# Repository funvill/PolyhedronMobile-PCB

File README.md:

# PolyhedronMobile-PCB

## Rhombic Dodecahedron

- Faces: `12 Rhombus`
- Acute angle: `70.53`
- Scale: `70mm`
- Long: `scale * (3/2)`
- Short: `scale * (3 * sqrt(2) / 4)`
- EdgeLength: `scale * (3 * sqrt(6) / 8)`

- https://en.wikipedia.org/wiki/Rhombic_dodecahedron
- http://dmccooey.com/polyhedra/RhombicDodecahedron.html

## Tetragonal Trapezohedron

[Tetragonal Trapezohedron Retrospective](https://blog.abluestar.com/tetragonal-trapezohedron-retrospective/)

- Faces: `8 kites`

- https://en.wikipedia.org/wiki/Tetragonal_trapezohedron

## Dodecahedron-pcb

[Dodecahedron PCB Retrospective](https://blog.abluestar.com/dodecahedron-pcb-retrospective/)

A [Regular dodecahedron](https://en.wikipedia.org/wiki/Regular_dodecahedron) is made of 12 regular [pentagonal](https://en.wikipedia.org/wiki/Pentagon) faces.

In this project 12 pentagon PCBs with LEDS are welded together using solder at the vertexs. The hole in the center is to insert the controller and batteries into the center.

More information can be found in this post. [Dodecahedron PCB Design](https://blog.abluestar.com/dodecahedron-pcb-design)

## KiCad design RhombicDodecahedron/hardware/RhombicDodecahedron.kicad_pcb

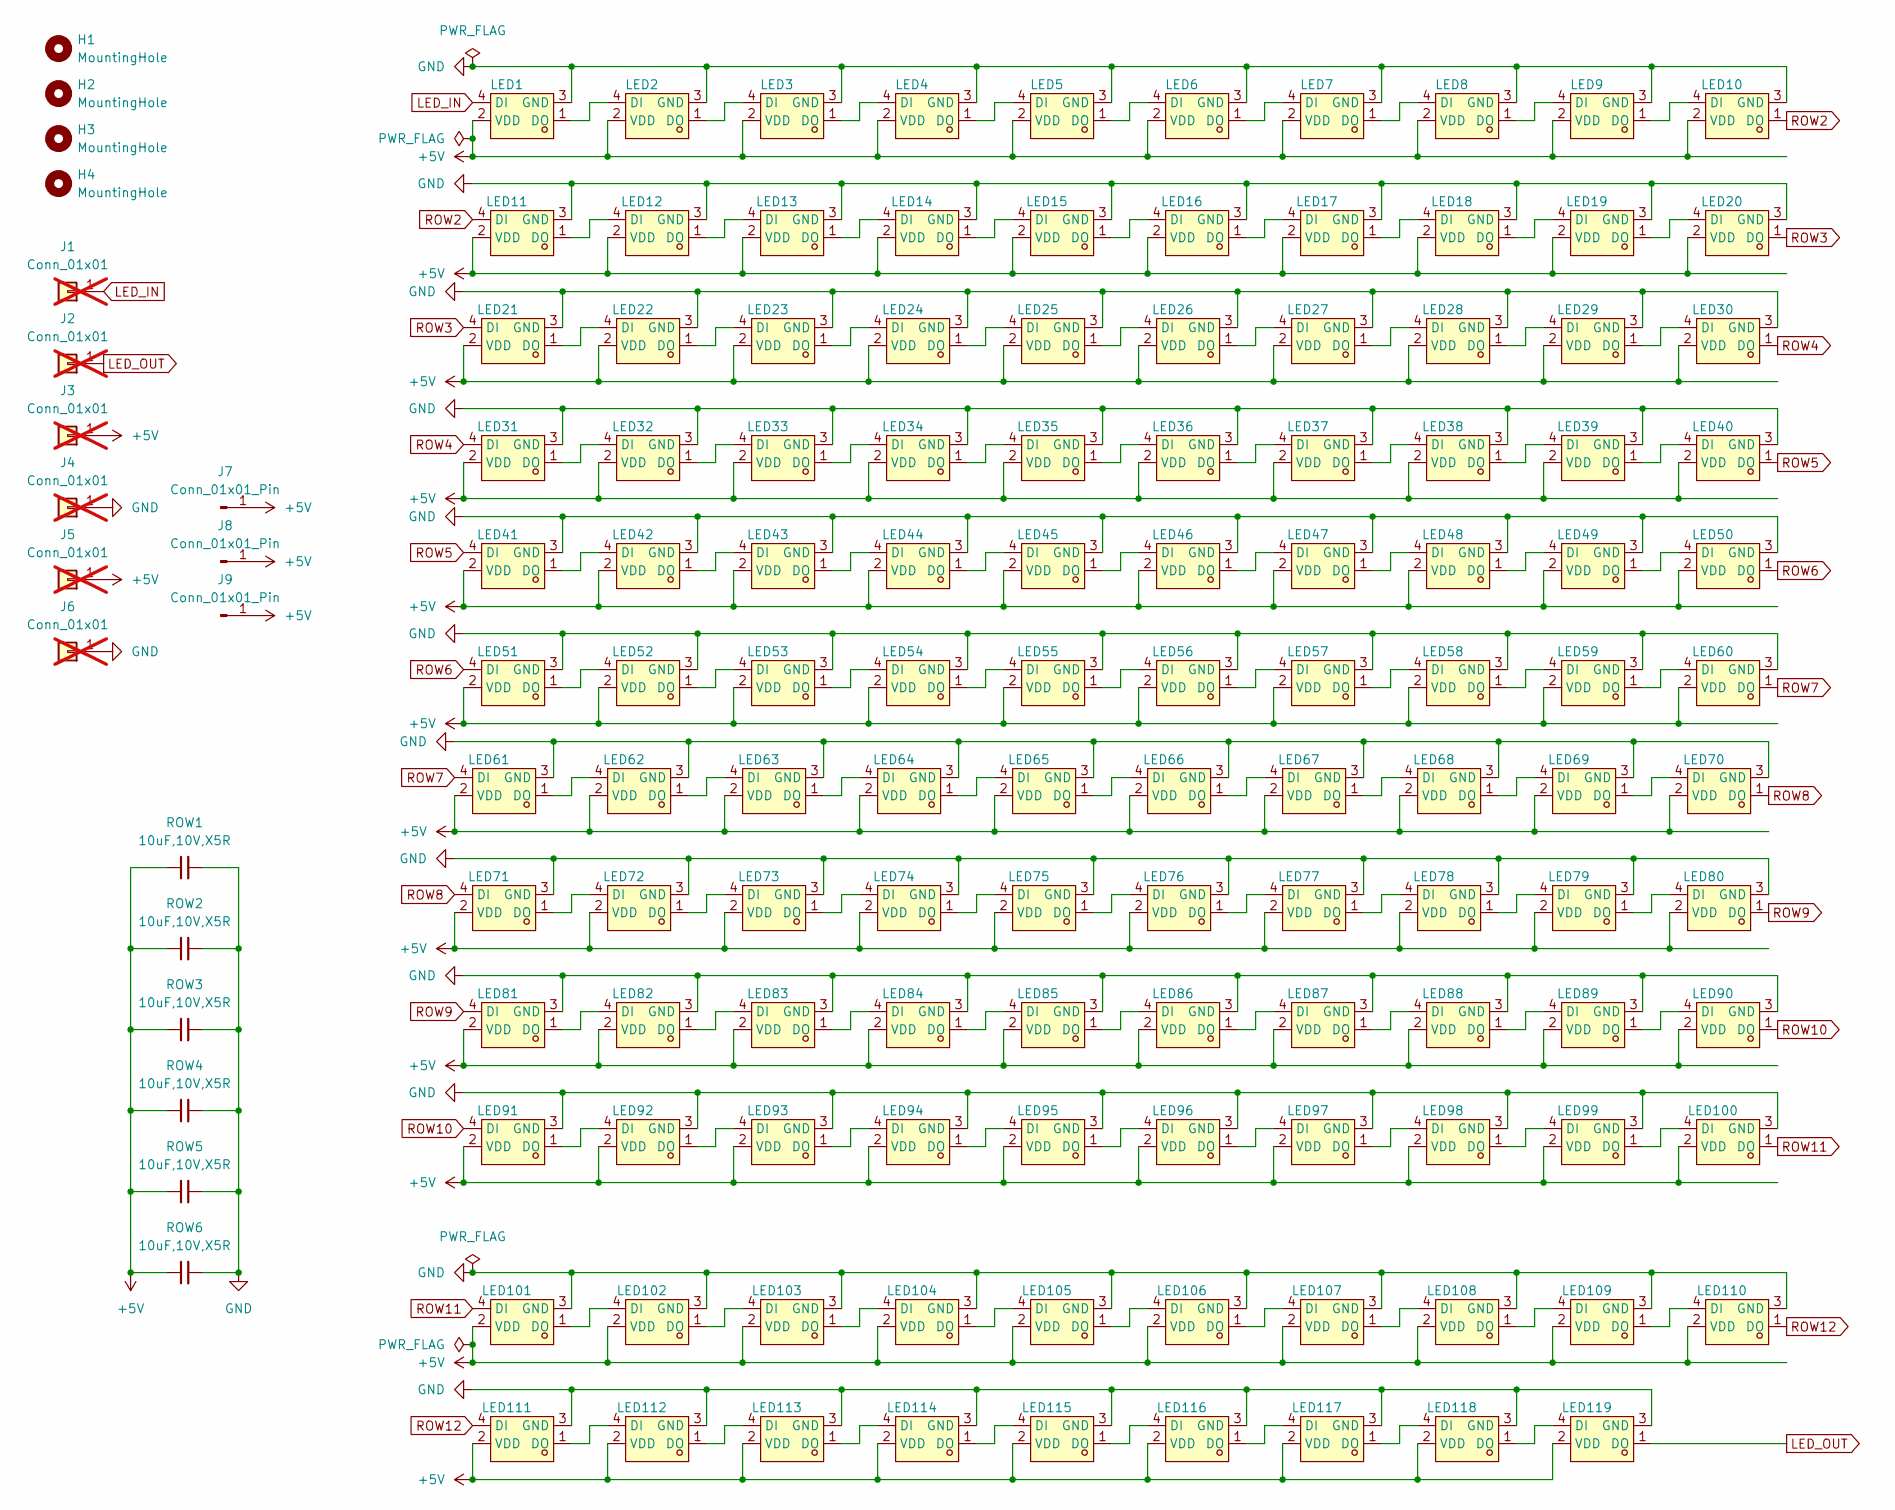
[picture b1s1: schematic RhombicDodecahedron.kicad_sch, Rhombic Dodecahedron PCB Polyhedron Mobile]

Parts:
H1, H2, H3, H4: MountingHole; MountingHole_3.2mm_M3
J1, J2, J3, J4, J5, J6: Conn_01x01; Pin_1x01_P2.54mm; not fitted
J7, J8, J9: Conn_01x01_Pin; Pin_1x01_P2.54mm_smt
LED1, LED2, LED3, LED4, LED5, LED6, LED7, LED8, LED9, LED10, LED11, LED12, LED13, LED14, LED15, LED16, LED17, LED18, LED19, LED20, LED21, LED22, LED23, LED24, LED25, LED26, LED27, LED28, LED29, LED30, LED31, LED32, LED33, LED34, LED35, LED36, LED37, LED38, LED39, LED40, LED41, LED42, LED43, LED44, LED45, LED46, LED47, LED48, LED49, LED50, LED51, LED52, LED53, LED54, LED55, LED56, LED57, LED58, LED59, LED60, LED61, LED62, LED63, LED64, LED65, LED66, LED67, LED68, LED69, LED70, LED71, LED72, LED73, LED74, LED75, LED76, LED77, LED78, LED79, LED80, LED81, LED82, LED83, LED84, LED85, LED86, LED87, LED88, LED89, LED90, LED91, LED92, LED93, LED94, LED95, LED96, LED97, LED98, LED99, LED100, LED101, LED102, LED103, LED104, LED105, LED106, LED107, LED108, LED109, LED110, LED111, LED112, LED113, LED114, LED115, LED116, LED117, LED118, LED119: XL-1615RGBC-WS2812B; LED-SMD_4P-L1.6-W1.5_XL-1615RGBC-WS2812B; LCSC Part C5349954
ROW1, ROW2, ROW3, ROW4, ROW5, ROW6: 10uF,10V,X5R; C_0402_1005Metric; MFGPN CL05A105KA5NQNC; LCSC C52923

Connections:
+5V: J3.1, J5.1, J7.1, J8.1, J9.1, LED1.2 (VDD), LED2.2 (VDD), LED3.2 (VDD), LED4.2 (VDD), LED5.2 (VDD), LED6.2 (VDD), LED7.2 (VDD), LED8.2 (VDD), LED9.2 (VDD), LED10.2 (VDD), LED11.2 (VDD), LED12.2 (VDD), LED13.2 (VDD), LED14.2 (VDD), LED15.2 (VDD), LED16.2 (VDD), LED17.2 (VDD), LED18.2 (VDD), LED19.2 (VDD), LED20.2 (VDD), LED21.2 (VDD), LED22.2 (VDD), LED23.2 (VDD), LED24.2 (VDD), LED25.2 (VDD), LED26.2 (VDD), LED27.2 (VDD), LED28.2 (VDD), LED29.2 (VDD), LED30.2 (VDD), LED31.2 (VDD), LED32.2 (VDD), LED33.2 (VDD), LED34.2 (VDD), LED35.2 (VDD), LED36.2 (VDD), LED37.2 (VDD), LED38.2 (VDD), LED39.2 (VDD), LED40.2 (VDD), LED41.2 (VDD), LED42.2 (VDD), LED43.2 (VDD), LED44.2 (VDD), LED45.2 (VDD), LED46.2 (VDD), LED47.2 (VDD), LED48.2 (VDD), LED49.2 (VDD), LED50.2 (VDD), LED51.2 (VDD), LED52.2 (VDD), LED53.2 (VDD), LED54.2 (VDD), LED55.2 (VDD), LED56.2 (VDD), LED57.2 (VDD), LED58.2 (VDD), LED59.2 (VDD), LED60.2 (VDD), LED61.2 (VDD), LED62.2 (VDD), LED63.2 (VDD), LED64.2 (VDD), LED65.2 (VDD), LED66.2 (VDD), LED67.2 (VDD), LED68.2 (VDD), LED69.2 (VDD), LED70.2 (VDD), LED71.2 (VDD), LED72.2 (VDD), LED73.2 (VDD), LED74.2 (VDD), LED75.2 (VDD), LED76.2 (VDD), LED77.2 (VDD), LED78.2 (VDD), LED79.2 (VDD), LED80.2 (VDD), LED81.2 (VDD), LED82.2 (VDD), LED83.2 (VDD), LED84.2 (VDD), LED85.2 (VDD), LED86.2 (VDD), LED87.2 (VDD), LED88.2 (VDD), LED89.2 (VDD), LED90.2 (VDD), LED91.2 (VDD), LED92.2 (VDD), LED93.2 (VDD), LED94.2 (VDD), LED95.2 (VDD), LED96.2 (VDD), LED97.2 (VDD), LED98.2 (VDD), LED99.2 (VDD), LED100.2 (VDD), LED101.2 (VDD), LED102.2 (VDD), LED103.2 (VDD), LED104.2 (VDD), LED105.2 (VDD), LED106.2 (VDD), LED107.2 (VDD), LED108.2 (VDD), LED109.2 (VDD), LED110.2 (VDD), LED111.2 (VDD), LED112.2 (VDD), LED113.2 (VDD), LED114.2 (VDD), LED115.2 (VDD), LED116.2 (VDD), LED117.2 (VDD), LED118.2 (VDD), LED119.2 (VDD), ROW1.2, ROW2.2, ROW3.2, ROW4.2, ROW5.2, ROW6.2
GND: J4.1, J6.1, LED1.3 (GND), LED2.3 (GND), LED3.3 (GND), LED4.3 (GND), LED5.3 (GND), LED6.3 (GND), LED7.3 (GND), LED8.3 (GND), LED9.3 (GND), LED10.3 (GND), LED11.3 (GND), LED12.3 (GND), LED13.3 (GND), LED14.3 (GND), LED15.3 (GND), LED16.3 (GND), LED17.3 (GND), LED18.3 (GND), LED19.3 (GND), LED20.3 (GND), LED21.3 (GND), LED22.3 (GND), LED23.3 (GND), LED24.3 (GND), LED25.3 (GND), LED26.3 (GND), LED27.3 (GND), LED28.3 (GND), LED29.3 (GND), LED30.3 (GND), LED31.3 (GND), LED32.3 (GND), LED33.3 (GND), LED34.3 (GND), LED35.3 (GND), LED36.3 (GND), LED37.3 (GND), LED38.3 (GND), LED39.3 (GND), LED40.3 (GND), LED41.3 (GND), LED42.3 (GND), LED43.3 (GND), LED44.3 (GND), LED45.3 (GND), LED46.3 (GND), LED47.3 (GND), LED48.3 (GND), LED49.3 (GND), LED50.3 (GND), LED51.3 (GND), LED52.3 (GND), LED53.3 (GND), LED54.3 (GND), LED55.3 (GND), LED56.3 (GND), LED57.3 (GND), LED58.3 (GND), LED59.3 (GND), LED60.3 (GND), LED61.3 (GND), LED62.3 (GND), LED63.3 (GND), LED64.3 (GND), LED65.3 (GND), LED66.3 (GND), LED67.3 (GND), LED68.3 (GND), LED69.3 (GND), LED70.3 (GND), LED71.3 (GND), LED72.3 (GND), LED73.3 (GND), LED74.3 (GND), LED75.3 (GND), LED76.3 (GND), LED77.3 (GND), LED78.3 (GND), LED79.3 (GND), LED80.3 (GND), LED81.3 (GND), LED82.3 (GND), LED83.3 (GND), LED84.3 (GND), LED85.3 (GND), LED86.3 (GND), LED87.3 (GND), LED88.3 (GND), LED89.3 (GND), LED90.3 (GND), LED91.3 (GND), LED92.3 (GND), LED93.3 (GND), LED94.3 (GND), LED95.3 (GND), LED96.3 (GND), LED97.3 (GND), LED98.3 (GND), LED99.3 (GND), LED100.3 (GND), LED101.3 (GND), LED102.3 (GND), LED103.3 (GND), LED104.3 (GND), LED105.3 (GND), LED106.3 (GND), LED107.3 (GND), LED108.3 (GND), LED109.3 (GND), LED110.3 (GND), LED111.3 (GND), LED112.3 (GND), LED113.3 (GND), LED114.3 (GND), LED115.3 (GND), LED116.3 (GND), LED117.3 (GND), LED118.3 (GND), LED119.3 (GND), ROW1.1, ROW2.1, ROW3.1, ROW4.1, ROW5.1, ROW6.1
LED_IN: J1.1, LED1.4 (DI)
LED_OUT: J2.1, LED119.1 (DO)
unnamed: LED1.1 (DO), LED2.4 (DI)
unnamed: LED2.1 (DO), LED3.4 (DI)
unnamed: LED3.1 (DO), LED4.4 (DI)
unnamed: LED4.1 (DO), LED5.4 (DI)
unnamed: LED5.1 (DO), LED6.4 (DI)
unnamed: LED6.1 (DO), LED7.4 (DI)
unnamed: LED7.1 (DO), LED8.4 (DI)
unnamed: LED8.1 (DO), LED9.4 (DI)
unnamed: LED9.1 (DO), LED10.4 (DI)
unnamed: LED11.1 (DO), LED12.4 (DI)
unnamed: LED12.1 (DO), LED13.4 (DI)
unnamed: LED13.1 (DO), LED14.4 (DI)
unnamed: LED14.1 (DO), LED15.4 (DI)
unnamed: LED15.1 (DO), LED16.4 (DI)
unnamed: LED16.1 (DO), LED17.4 (DI)
unnamed: LED17.1 (DO), LED18.4 (DI)
unnamed: LED18.1 (DO), LED19.4 (DI)
unnamed: LED19.1 (DO), LED20.4 (DI)
unnamed: LED21.1 (DO), LED22.4 (DI)
unnamed: LED22.1 (DO), LED23.4 (DI)
unnamed: LED23.1 (DO), LED24.4 (DI)
unnamed: LED24.1 (DO), LED25.4 (DI)
unnamed: LED25.1 (DO), LED26.4 (DI)
unnamed: LED26.1 (DO), LED27.4 (DI)
unnamed: LED27.1 (DO), LED28.4 (DI)
unnamed: LED28.1 (DO), LED29.4 (DI)
unnamed: LED29.1 (DO), LED30.4 (DI)
unnamed: LED31.1 (DO), LED32.4 (DI)
unnamed: LED32.1 (DO), LED33.4 (DI)
unnamed: LED33.1 (DO), LED34.4 (DI)
unnamed: LED34.1 (DO), LED35.4 (DI)
unnamed: LED35.1 (DO), LED36.4 (DI)
unnamed: LED36.1 (DO), LED37.4 (DI)
unnamed: LED37.1 (DO), LED38.4 (DI)
unnamed: LED38.1 (DO), LED39.4 (DI)
unnamed: LED39.1 (DO), LED40.4 (DI)
unnamed: LED41.1 (DO), LED42.4 (DI)
unnamed: LED42.1 (DO), LED43.4 (DI)
unnamed: LED43.1 (DO), LED44.4 (DI)
unnamed: LED44.1 (DO), LED45.4 (DI)
unnamed: LED45.1 (DO), LED46.4 (DI)
unnamed: LED46.1 (DO), LED47.4 (DI)
unnamed: LED47.1 (DO), LED48.4 (DI)
unnamed: LED48.1 (DO), LED49.4 (DI)
unnamed: LED49.1 (DO), LED50.4 (DI)
unnamed: LED51.1 (DO), LED52.4 (DI)
unnamed: LED52.1 (DO), LED53.4 (DI)
unnamed: LED53.1 (DO), LED54.4 (DI)
unnamed: LED54.1 (DO), LED55.4 (DI)
unnamed: LED55.1 (DO), LED56.4 (DI)
unnamed: LED56.1 (DO), LED57.4 (DI)
unnamed: LED57.1 (DO), LED58.4 (DI)
unnamed: LED58.1 (DO), LED59.4 (DI)
unnamed: LED59.1 (DO), LED60.4 (DI)
unnamed: LED61.1 (DO), LED62.4 (DI)
unnamed: LED62.1 (DO), LED63.4 (DI)
unnamed: LED63.1 (DO), LED64.4 (DI)
unnamed: LED64.1 (DO), LED65.4 (DI)
unnamed: LED65.1 (DO), LED66.4 (DI)
unnamed: LED66.1 (DO), LED67.4 (DI)
unnamed: LED67.1 (DO), LED68.4 (DI)
unnamed: LED68.1 (DO), LED69.4 (DI)
unnamed: LED69.1 (DO), LED70.4 (DI)
unnamed: LED71.1 (DO), LED72.4 (DI)
unnamed: LED72.1 (DO), LED73.4 (DI)
unnamed: LED73.1 (DO), LED74.4 (DI)
unnamed: LED74.1 (DO), LED75.4 (DI)
unnamed: LED75.1 (DO), LED76.4 (DI)
unnamed: LED76.1 (DO), LED77.4 (DI)
unnamed: LED77.1 (DO), LED78.4 (DI)
unnamed: LED78.1 (DO), LED79.4 (DI)
unnamed: LED79.1 (DO), LED80.4 (DI)
unnamed: LED81.1 (DO), LED82.4 (DI)
unnamed: LED82.1 (DO), LED83.4 (DI)
unnamed: LED83.1 (DO), LED84.4 (DI)
unnamed: LED84.1 (DO), LED85.4 (DI)
unnamed: LED85.1 (DO), LED86.4 (DI)
unnamed: LED86.1 (DO), LED87.4 (DI)
unnamed: LED87.1 (DO), LED88.4 (DI)
unnamed: LED88.1 (DO), LED89.4 (DI)
unnamed: LED89.1 (DO), LED90.4 (DI)
unnamed: LED91.1 (DO), LED92.4 (DI)
unnamed: LED92.1 (DO), LED93.4 (DI)
unnamed: LED93.1 (DO), LED94.4 (DI)
unnamed: LED94.1 (DO), LED95.4 (DI)
unnamed: LED95.1 (DO), LED96.4 (DI)
unnamed: LED96.1 (DO), LED97.4 (DI)
unnamed: LED97.1 (DO), LED98.4 (DI)
unnamed: LED98.1 (DO), LED99.4 (DI)
unnamed: LED99.1 (DO), LED100.4 (DI)
unnamed: LED101.1 (DO), LED102.4 (DI)
unnamed: LED102.1 (DO), LED103.4 (DI)
unnamed: LED103.1 (DO), LED104.4 (DI)
unnamed: LED104.1 (DO), LED105.4 (DI)
unnamed: LED105.1 (DO), LED106.4 (DI)
unnamed: LED106.1 (DO), LED107.4 (DI)
unnamed: LED107.1 (DO), LED108.4 (DI)
unnamed: LED108.1 (DO), LED109.4 (DI)
unnamed: LED109.1 (DO), LED110.4 (DI)
unnamed: LED111.1 (DO), LED112.4 (DI)
unnamed: LED112.1 (DO), LED113.4 (DI)
unnamed: LED113.1 (DO), LED114.4 (DI)
unnamed: LED114.1 (DO), LED115.4 (DI)
unnamed: LED115.1 (DO), LED116.4 (DI)
unnamed: LED116.1 (DO), LED117.4 (DI)
unnamed: LED117.1 (DO), LED118.4 (DI)
unnamed: LED118.1 (DO), LED119.4 (DI)
ROW2: LED10.1 (DO), LED11.4 (DI)
ROW3: LED20.1 (DO), LED21.4 (DI)
ROW4: LED30.1 (DO), LED31.4 (DI)
ROW5: LED40.1 (DO), LED41.4 (DI)
ROW6: LED50.1 (DO), LED51.4 (DI)
ROW7: LED60.1 (DO), LED61.4 (DI)
ROW8: LED70.1 (DO), LED71.4 (DI)
ROW9: LED80.1 (DO), LED81.4 (DI)
ROW10: LED90.1 (DO), LED91.4 (DI)
ROW11: LED100.1 (DO), LED101.4 (DI)
ROW12: LED110.1 (DO), LED111.4 (DI)

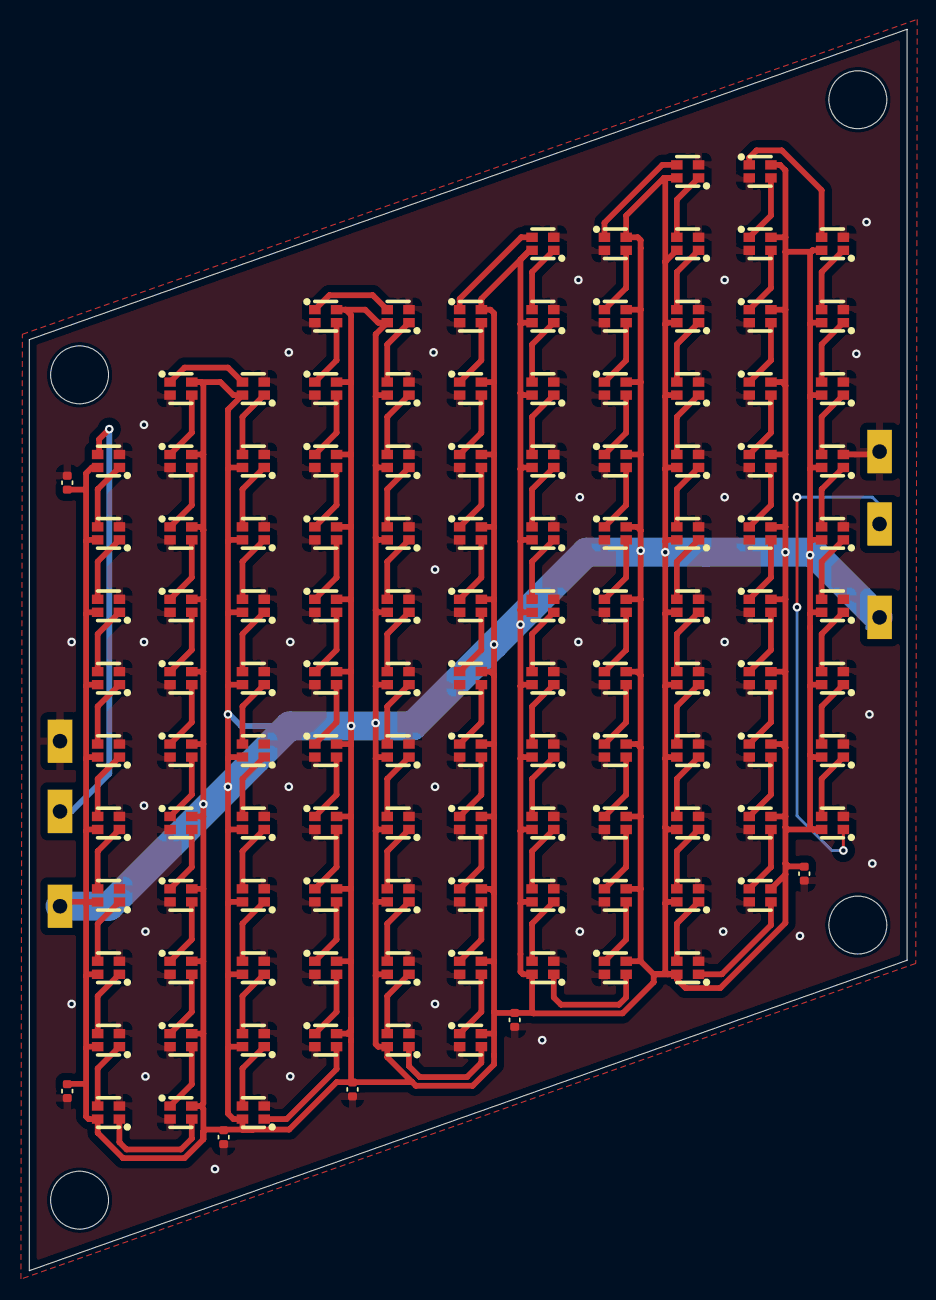
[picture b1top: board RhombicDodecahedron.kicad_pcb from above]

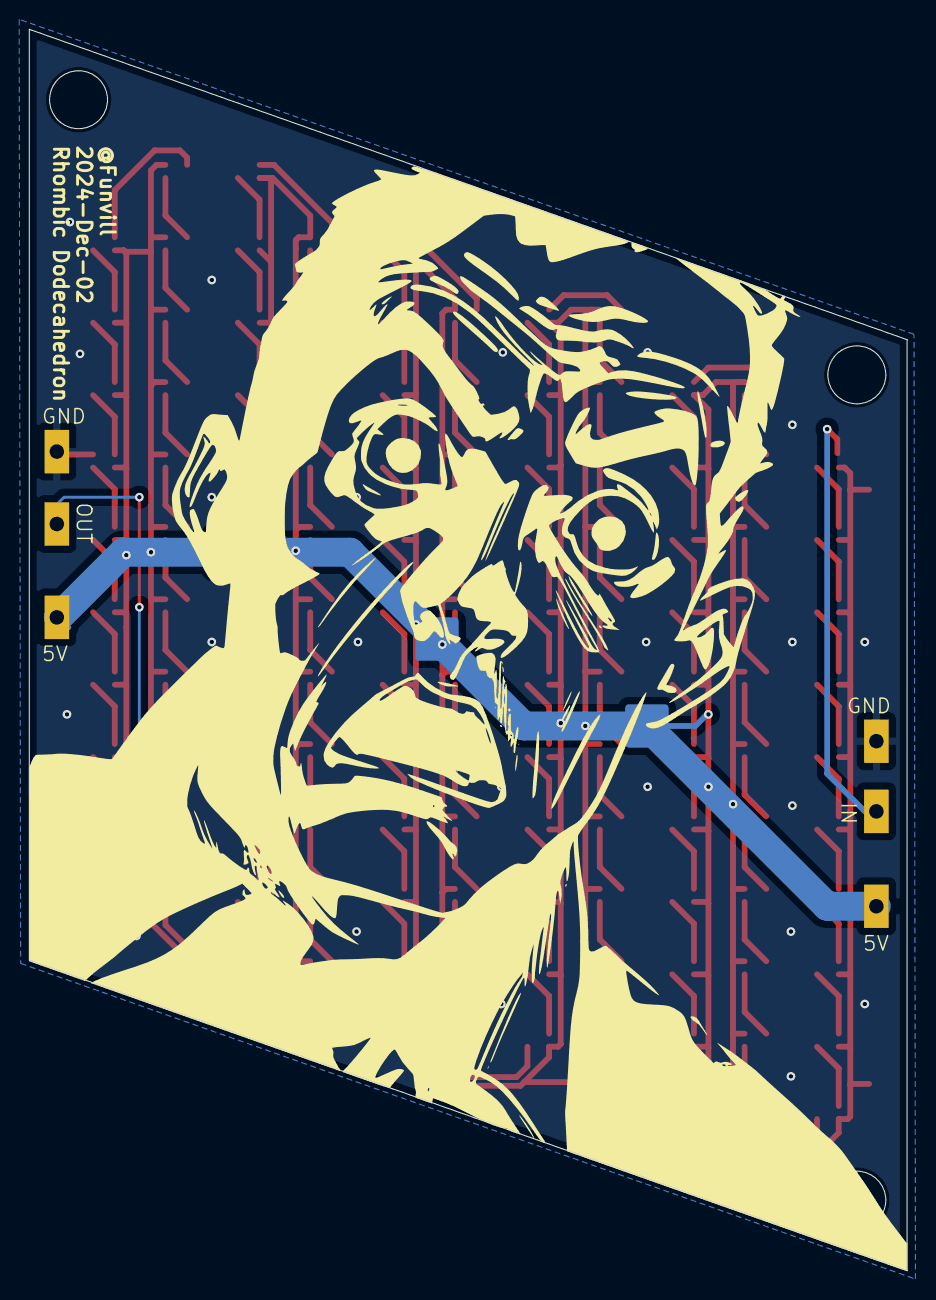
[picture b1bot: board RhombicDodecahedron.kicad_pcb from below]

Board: 2 copper layers, 60.6 x 85.7 mm, 138 parts (3 on the bottom side), 122 nets.

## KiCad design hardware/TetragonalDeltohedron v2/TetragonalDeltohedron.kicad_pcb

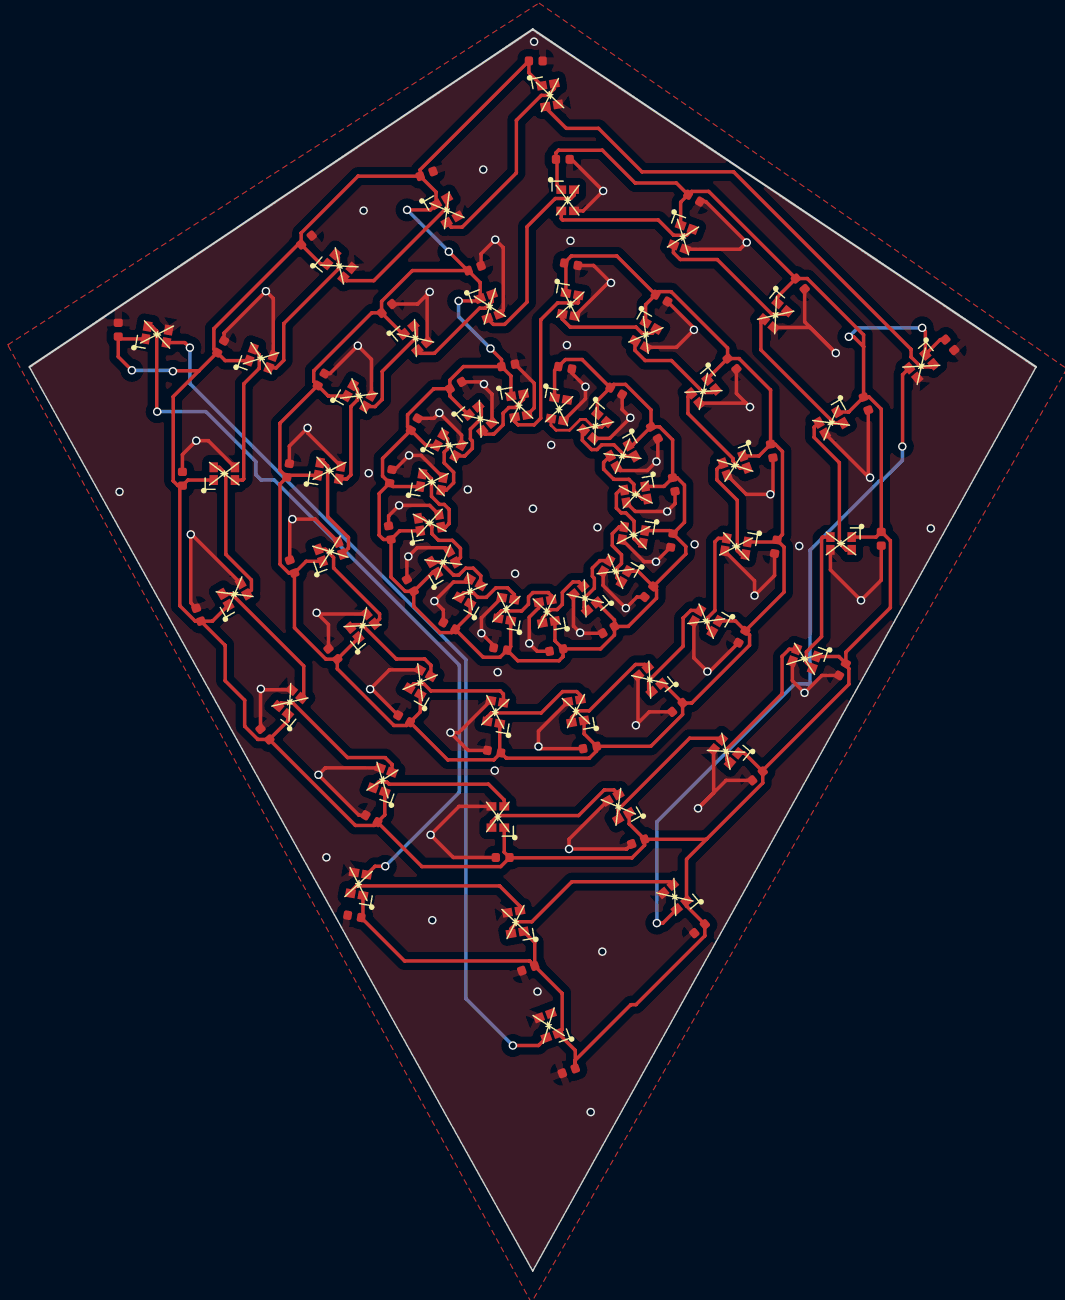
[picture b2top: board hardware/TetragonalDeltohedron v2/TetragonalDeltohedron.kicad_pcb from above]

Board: 2 copper layers, 71.1 x 87.7 mm, 110 parts (0 on the bottom side), 56 nets.

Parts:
C1, C2, C3, C4, C5, C6, C7, C8, C9, C10, C11, C12, C13, C14, C15, C16, C17, C18, C19, C20, C21, C22, C23, C24, C25, C26, C27, C28, C29, C30, C31, C32, C33, C34, C35, C36, C37, C38, C39, C40, C41, C42, C43, C44, C45, C46, C47, C48, C49, C50, C51, C52, C53, C54, C55: 1uF,25V,X5R; C_0402_1005Metric
U1, U2, U3, U4, U5, U6, U7, U8, U9, U10, U11, U12, U13, U14, U15, U16, U17, U18, U19, U20, U21, U22, U23, U24, U25, U26, U27, U28, U29, U30, U31, U32, U33, U34, U35, U36, U37, U38, U39, U40, U41, U42, U43, U44, U45, U46, U47, U48, U49, U50, U51, U52, U53, U54, U55: XL-0807RGBC-WS2812B

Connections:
+5V: C1.1, C2.1, C3.1, C4.1, C5.1, C6.1, C7.1, C8.1, C9.1, C10.1, C11.1, C12.1, C13.1, C14.1, C15.1, C16.1, C17.1, C18.1, C19.1, C20.1, C21.1, C22.1, C23.1, C24.1, C25.1, C26.1, C27.1, C28.1, C29.1, C30.1, C31.1, C32.1, C33.1, C34.1, C35.1, C36.1, C37.1, C38.1, C39.1, C40.1, C41.1, C42.1, C43.1, C44.1, C45.1, C46.1, C47.1, C48.1, C49.1, C50.1, C51.1, C52.1, C53.1, C54.1, C55.1, U1.1 (VDD), U2.1 (VDD), U3.1 (VDD), U4.1 (VDD), U5.1 (VDD), U6.1 (VDD), U7.1 (VDD), U8.1 (VDD), U9.1 (VDD), U10.1 (VDD), U11.1 (VDD), U12.1 (VDD), U13.1 (VDD), U14.1 (VDD), U15.1 (VDD), U16.1 (VDD), U17.1 (VDD), U18.1 (VDD), U19.1 (VDD), U20.1 (VDD), U21.1 (VDD), U22.1 (VDD), U23.1 (VDD), U24.1 (VDD), U25.1 (VDD), U26.1 (VDD), U27.1 (VDD), U28.1 (VDD), U29.1 (VDD), U30.1 (VDD), U31.1 (VDD), U32.1 (VDD), U33.1 (VDD), U34.1 (VDD), U35.1 (VDD), U36.1 (VDD), U37.1 (VDD), U38.1 (VDD), U39.1 (VDD), U40.1 (VDD), U41.1 (VDD), U42.1 (VDD), U43.1 (VDD), U44.1 (VDD), U45.1 (VDD), U46.1 (VDD), U47.1 (VDD), U48.1 (VDD), U49.1 (VDD), U50.1 (VDD), U51.1 (VDD), U52.1 (VDD), U53.1 (VDD), U54.1 (VDD), U55.1 (VDD)
GND: C1.2, C2.2, C3.2, C4.2, C5.2, C6.2, C7.2, C8.2, C9.2, C10.2, C11.2, C12.2, C13.2, C14.2, C15.2, C16.2, C17.2, C18.2, C19.2, C20.2, C21.2, C22.2, C23.2, C24.2, C25.2, C26.2, C27.2, C28.2, C29.2, C30.2, C31.2, C32.2, C33.2, C34.2, C35.2, C36.2, C37.2, C38.2, C39.2, C40.2, C41.2, C42.2, C43.2, C44.2, C45.2, C46.2, C47.2, C48.2, C49.2, C50.2, C51.2, C52.2, C53.2, C54.2, C55.2, U1.3 (GND), U2.3 (GND), U3.3 (GND), U4.3 (GND), U5.3 (GND), U6.3 (GND), U7.3 (GND), U8.3 (GND), U9.3 (GND), U10.3 (GND), U11.3 (GND), U12.3 (GND), U13.3 (GND), U14.3 (GND), U15.3 (GND), U16.3 (GND), U17.3 (GND), U18.3 (GND), U19.3 (GND), U20.3 (GND), U21.3 (GND), U22.3 (GND), U23.3 (GND), U24.3 (GND), U25.3 (GND), U26.3 (GND), U27.3 (GND), U28.3 (GND), U29.3 (GND), U30.3 (GND), U31.3 (GND), U32.3 (GND), U33.3 (GND), U34.3 (GND), U35.3 (GND), U36.3 (GND), U37.3 (GND), U38.3 (GND), U39.3 (GND), U40.3 (GND), U41.3 (GND), U42.3 (GND), U43.3 (GND), U44.3 (GND), U45.3 (GND), U46.3 (GND), U47.3 (GND), U48.3 (GND), U49.3 (GND), U50.3 (GND), U51.3 (GND), U52.3 (GND), U53.3 (GND), U54.3 (GND), U55.3 (GND)
unnamed: U1.2 (DOUT), U2.4 (DIN)
unnamed: U2.2 (DOUT), U3.4 (DIN)
unnamed: U3.2 (DOUT), U4.4 (DIN)
unnamed: U4.2 (DOUT), U5.4 (DIN)
unnamed: U5.2 (DOUT), U6.4 (DIN)
unnamed: U6.2 (DOUT), U7.4 (DIN)
unnamed: U7.2 (DOUT), U8.4 (DIN)
unnamed: U8.2 (DOUT), U9.4 (DIN)
unnamed: U9.2 (DOUT), U10.4 (DIN)
unnamed: U10.2 (DOUT), U11.4 (DIN)
unnamed: U11.2 (DOUT), U12.4 (DIN)
unnamed: U12.2 (DOUT), U13.4 (DIN)
unnamed: U13.2 (DOUT), U14.4 (DIN)
unnamed: U14.2 (DOUT), U15.4 (DIN)
unnamed: U15.2 (DOUT), U16.4 (DIN)
unnamed: U17.2 (DOUT), U18.4 (DIN)
unnamed: U18.2 (DOUT), U19.4 (DIN)
unnamed: U19.2 (DOUT), U20.4 (DIN)
unnamed: U20.2 (DOUT), U21.4 (DIN)
unnamed: U21.2 (DOUT), U22.4 (DIN)
unnamed: U22.2 (DOUT), U23.4 (DIN)
unnamed: U23.2 (DOUT), U24.4 (DIN)
unnamed: U24.2 (DOUT), U25.4 (DIN)
unnamed: U25.2 (DOUT), U26.4 (DIN)
unnamed: U26.2 (DOUT), U27.4 (DIN)
unnamed: U27.2 (DOUT), U28.4 (DIN)
unnamed: U28.2 (DOUT), U29.4 (DIN)
unnamed: U29.2 (DOUT), U30.4 (DIN)
unnamed: U30.2 (DOUT), U31.4 (DIN)
unnamed: U31.2 (DOUT), U32.4 (DIN)
unnamed: U33.2 (DOUT), U34.4 (DIN)
unnamed: U34.2 (DOUT), U35.4 (DIN)
unnamed: U35.2 (DOUT), U36.4 (DIN)
unnamed: U36.2 (DOUT), U37.4 (DIN)
unnamed: U37.2 (DOUT), U38.4 (DIN)
unnamed: U38.2 (DOUT), U39.4 (DIN)
unnamed: U39.2 (DOUT), U40.4 (DIN)
unnamed: U40.2 (DOUT), U41.4 (DIN)
unnamed: U41.2 (DOUT), U42.4 (DIN)
unnamed: U42.2 (DOUT), U43.4 (DIN)
unnamed: U43.2 (DOUT), U44.4 (DIN)
unnamed: U44.2 (DOUT), U45.4 (DIN)
unnamed: U45.2 (DOUT), U46.4 (DIN)
unnamed: U46.2 (DOUT), U47.4 (DIN)
unnamed: U47.2 (DOUT), U48.4 (DIN)
unnamed: U49.2 (DOUT), U50.4 (DIN)
unnamed: U50.2 (DOUT), U51.4 (DIN)
unnamed: U51.2 (DOUT), U52.4 (DIN)
unnamed: U52.2 (DOUT), U53.4 (DIN)
unnamed: U53.2 (DOUT), U54.4 (DIN)
unnamed: U54.2 (DOUT), U55.4 (DIN)
ROW_02: U16.2 (DOUT), U17.4 (DIN)
ROW_03: U32.2 (DOUT), U33.4 (DIN)
ROW_04: U48.2 (DOUT), U49.4 (DIN)

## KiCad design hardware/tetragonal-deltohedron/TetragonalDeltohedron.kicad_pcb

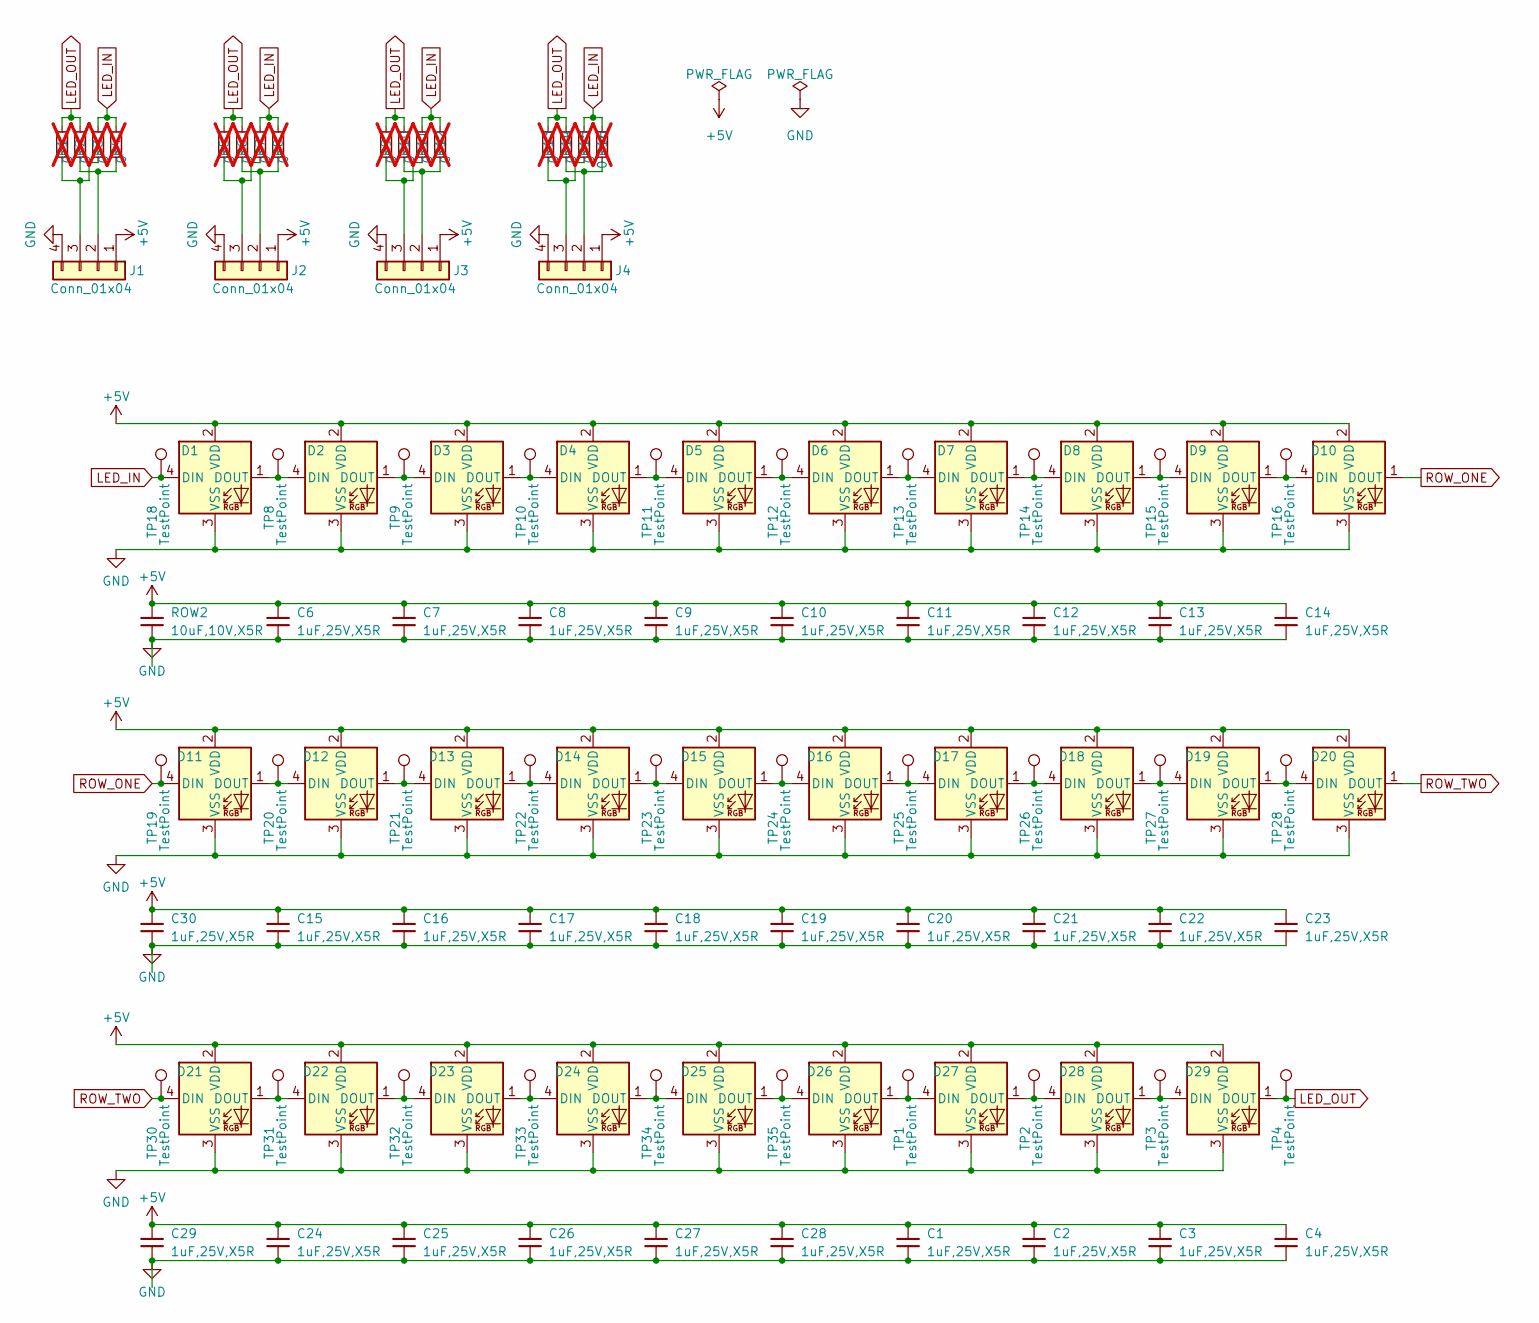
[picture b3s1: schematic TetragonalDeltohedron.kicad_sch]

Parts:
C1, C2, C3, C4, C6, C7, C8, C9, C10, C11, C12, C13, C14, C15, C16, C17, C18, C19, C20, C21, C22, C23, C24, C25, C26, C27, C28, C29, C30: 1uF,25V,X5R; C_0603_1608Metric; MFGPN CL05A105KA5NQNC; LCSC C52923
D1, D2, D3, D4, D5, D6, D7, D8, D9, D10, D11, D12, D13, D14, D15, D16, D17, D18, D19, D20, D21, D22, D23, D24, D25, D26, D27, D28, D29: XL-1010RGBC-WS2812B; LCSC C5349953
J1, J2, J3, J4: Conn_01x04; dodecahedron_corner
R1, R2, R3, R4, R5, R6, R7, R8, R9, R10, R11, R12, R13, R14, R15, R16: 0; R_0402_1005Metric; MFGPN 0402WGF0000TCE; LCSC C17168; not fitted
ROW2: 10uF,10V,X5R; C_0603_1608Metric; MFGPN CL05A105KA5NQNC; LCSC C52923
TP1, TP2, TP3, TP4, TP8, TP9, TP10, TP11, TP12, TP13, TP14, TP15, TP16, TP18, TP19, TP20, TP21, TP22, TP23, TP24, TP25, TP26, TP27, TP28, TP30, TP31, TP32, TP33, TP34, TP35: TestPoint; SWS-Testpoint-Bug-SM-2.4mm

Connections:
+5V: C1.1, C2.1, C3.1, C4.1, C6.1, C7.1, C8.1, C9.1, C10.1, C11.1, C12.1, C13.1, C14.1, C15.1, C16.1, C17.1, C18.1, C19.1, C20.1, C21.1, C22.1, C23.1, C24.1, C25.1, C26.1, C27.1, C28.1, C29.1, C30.1, D1.2 (VDD), D2.2 (VDD), D3.2 (VDD), D4.2 (VDD), D5.2 (VDD), D6.2 (VDD), D7.2 (VDD), D8.2 (VDD), D9.2 (VDD), D10.2 (VDD), D11.2 (VDD), D12.2 (VDD), D13.2 (VDD), D14.2 (VDD), D15.2 (VDD), D16.2 (VDD), D17.2 (VDD), D18.2 (VDD), D19.2 (VDD), D20.2 (VDD), D21.2 (VDD), D22.2 (VDD), D23.2 (VDD), D24.2 (VDD), D25.2 (VDD), D26.2 (VDD), D27.2 (VDD), D28.2 (VDD), D29.2 (VDD), J1.1, J2.1, J3.1, J4.1, ROW2.2
GND: C1.2, C2.2, C3.2, C4.2, C6.2, C7.2, C8.2, C9.2, C10.2, C11.2, C12.2, C13.2, C14.2, C15.2, C16.2, C17.2, C18.2, C19.2, C20.2, C21.2, C22.2, C23.2, C24.2, C25.2, C26.2, C27.2, C28.2, C29.2, C30.2, D1.3 (VSS), D2.3 (VSS), D3.3 (VSS), D4.3 (VSS), D5.3 (VSS), D6.3 (VSS), D7.3 (VSS), D8.3 (VSS), D9.3 (VSS), D10.3 (VSS), D11.3 (VSS), D12.3 (VSS), D13.3 (VSS), D14.3 (VSS), D15.3 (VSS), D16.3 (VSS), D17.3 (VSS), D18.3 (VSS), D19.3 (VSS), D20.3 (VSS), D21.3 (VSS), D22.3 (VSS), D23.3 (VSS), D24.3 (VSS), D25.3 (VSS), D26.3 (VSS), D27.3 (VSS), D28.3 (VSS), D29.3 (VSS), J1.4, J2.4, J3.4, J4.4, ROW2.1
LED_IN: D1.4 (DIN), R3.1, R4.1, R7.1, R8.1, R11.1, R12.1, R15.1, R16.1, TP18.1
LED_OUT: D29.1 (DOUT), R1.1, R2.1, R5.1, R6.1, R9.1, R10.1, R13.1, R14.1, TP4.1
unnamed: D1.1 (DOUT), D2.4 (DIN), TP8.1
unnamed: D2.1 (DOUT), D3.4 (DIN), TP9.1
unnamed: D3.1 (DOUT), D4.4 (DIN), TP10.1
unnamed: D4.1 (DOUT), D5.4 (DIN), TP11.1
unnamed: D5.1 (DOUT), D6.4 (DIN), TP12.1
unnamed: D6.1 (DOUT), D7.4 (DIN), TP13.1
unnamed: D7.1 (DOUT), D8.4 (DIN), TP14.1
unnamed: D8.1 (DOUT), D9.4 (DIN), TP15.1
unnamed: D9.1 (DOUT), D10.4 (DIN), TP16.1
unnamed: D11.1 (DOUT), D12.4 (DIN), TP20.1
unnamed: D12.1 (DOUT), D13.4 (DIN), TP21.1
unnamed: D13.1 (DOUT), D14.4 (DIN), TP22.1
unnamed: D14.1 (DOUT), D15.4 (DIN), TP23.1
unnamed: D15.1 (DOUT), D16.4 (DIN), TP24.1
unnamed: D16.1 (DOUT), D17.4 (DIN), TP25.1
unnamed: D17.1 (DOUT), D18.4 (DIN), TP26.1
unnamed: D18.1 (DOUT), D19.4 (DIN), TP27.1
unnamed: D19.1 (DOUT), D20.4 (DIN), TP28.1
unnamed: D21.1 (DOUT), D22.4 (DIN), TP31.1
unnamed: D22.1 (DOUT), D23.4 (DIN), TP32.1
unnamed: D23.1 (DOUT), D24.4 (DIN), TP33.1
unnamed: D24.1 (DOUT), D25.4 (DIN), TP34.1
unnamed: D25.1 (DOUT), D26.4 (DIN), TP35.1
unnamed: D26.1 (DOUT), D27.4 (DIN), TP1.1
unnamed: D27.1 (DOUT), D28.4 (DIN), TP2.1
unnamed: D28.1 (DOUT), D29.4 (DIN), TP3.1
unnamed: J1.2, R2.2, R4.2
unnamed: J1.3, R1.2, R3.2
unnamed: J2.2, R6.2, R8.2
unnamed: J2.3, R5.2, R7.2
unnamed: J3.2, R10.2, R12.2
unnamed: J3.3, R9.2, R11.2
unnamed: J4.2, R14.2, R16.2
unnamed: J4.3, R13.2, R15.2
ROW_ONE: D10.1 (DOUT), D11.4 (DIN), TP19.1
ROW_TWO: D20.1 (DOUT), D21.4 (DIN), TP30.1

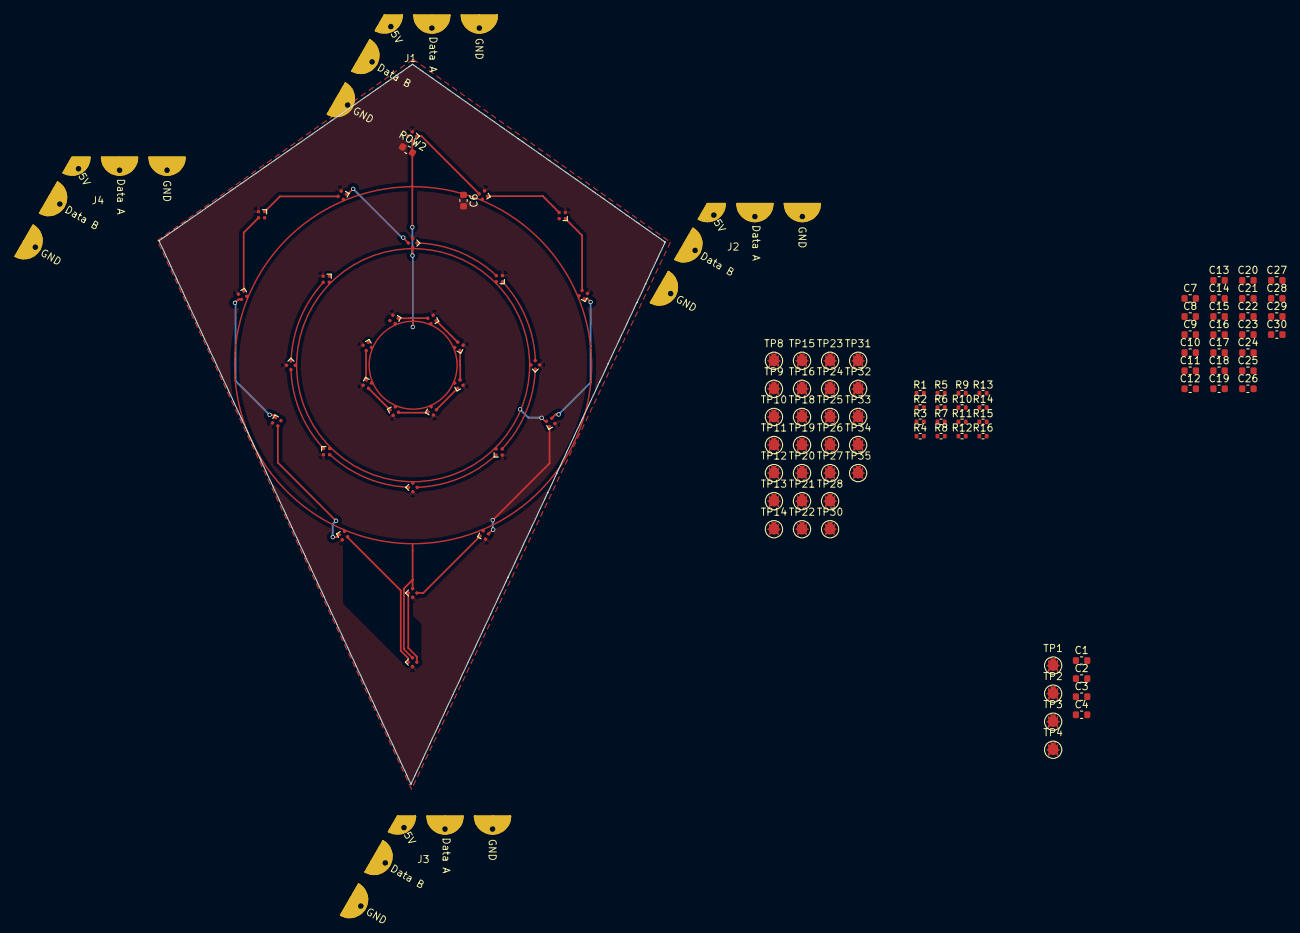
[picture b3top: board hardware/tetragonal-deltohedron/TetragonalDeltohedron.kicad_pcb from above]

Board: 2 copper layers, 70.3 x 100.0 mm, 109 parts (0 on the bottom side), 40 nets.

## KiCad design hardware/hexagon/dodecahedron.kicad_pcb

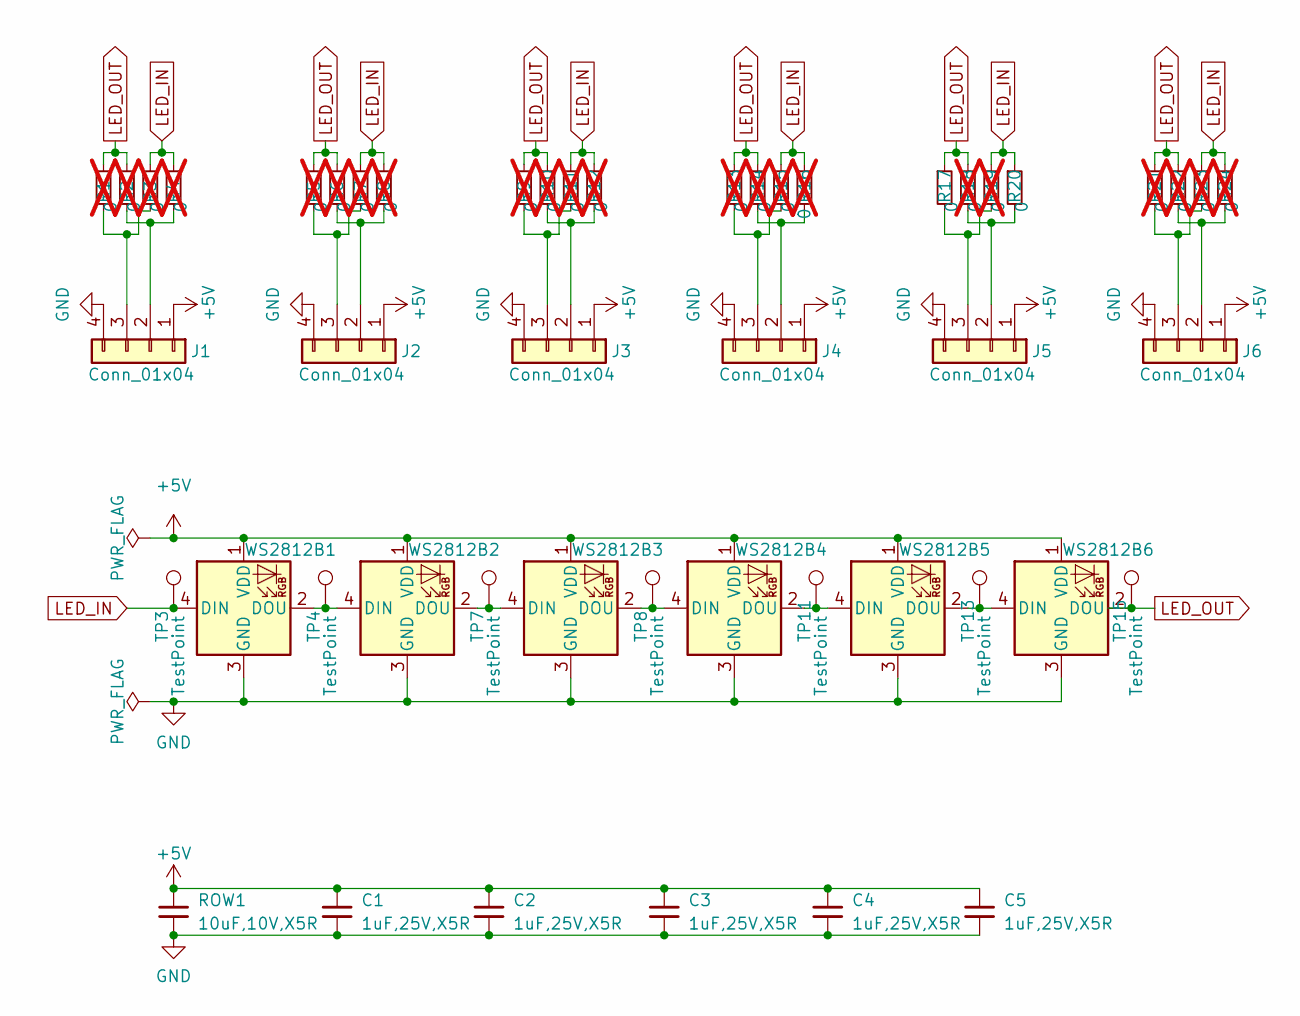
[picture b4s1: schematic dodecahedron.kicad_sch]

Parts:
C1, C2, C3, C4, C5: 1uF,25V,X5R; C_0603_1608Metric; MFGPN CL05A105KA5NQNC; LCSC C52923
J1, J2, J3, J4, J5, J6: Conn_01x04; dodecahedron_corner
R1, R2, R3, R4, R5, R6, R7, R8, R9, R10, R11, R12, R13, R14, R15, R16, R18, R19, R21, R22, R23, R24: 0; R_0402_1005Metric; MFGPN 0402WGF0000TCE; LCSC C17168; not fitted
R17, R20: 0; R_0402_1005Metric; MFGPN 0402WGF0000TCE; LCSC C17168
ROW1: 10uF,10V,X5R; C_0603_1608Metric; MFGPN CL05A105KA5NQNC; LCSC C52923
TP3, TP4, TP7, TP8, TP11, TP13, TP15: TestPoint; SWS-Testpoint-Bug-SM-2.4mm
WS2812B1, WS2812B2, WS2812B3, WS2812B4, WS2812B5, WS2812B6: XL-5050RGBC-WS2812B; LED_WS2812B_PLCC4_5.0x5.0mm_P3.2mm; LCSC C2843785

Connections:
+5V: C1.1, C2.1, C3.1, C4.1, C5.1, J1.1, J2.1, J3.1, J4.1, J5.1, J6.1, ROW1.2, WS2812B1.1 (VDD), WS2812B2.1 (VDD), WS2812B3.1 (VDD), WS2812B4.1 (VDD), WS2812B5.1 (VDD), WS2812B6.1 (VDD)
GND: C1.2, C2.2, C3.2, C4.2, C5.2, J1.4, J2.4, J3.4, J4.4, J5.4, J6.4, ROW1.1, WS2812B1.3 (GND), WS2812B2.3 (GND), WS2812B3.3 (GND), WS2812B4.3 (GND), WS2812B5.3 (GND), WS2812B6.3 (GND)
LED_IN: R3.1, R4.1, R7.1, R8.1, R11.1, R12.1, R15.1, R16.1, R19.1, R20.1, R23.1, R24.1, TP3.1, WS2812B1.4 (DIN)
LED_OUT: R1.1, R2.1, R5.1, R6.1, R9.1, R10.1, R13.1, R14.1, R17.1, R18.1, R21.1, R22.1, TP15.1, WS2812B6.2 (DOU)
unnamed: J1.2, R2.2, R4.2
unnamed: J1.3, R1.2, R3.2
unnamed: J2.2, R6.2, R8.2
unnamed: J2.3, R5.2, R7.2
unnamed: J3.2, R10.2, R12.2
unnamed: J3.3, R9.2, R11.2
unnamed: J4.2, R14.2, R16.2
unnamed: J4.3, R13.2, R15.2
unnamed: J5.2, R18.2, R20.2
unnamed: J5.3, R17.2, R19.2
unnamed: J6.2, R22.2, R24.2
unnamed: J6.3, R21.2, R23.2
unnamed: TP4.1, WS2812B1.2 (DOU), WS2812B2.4 (DIN)
unnamed: TP7.1, WS2812B2.2 (DOU), WS2812B3.4 (DIN)
unnamed: TP8.1, WS2812B3.2 (DOU), WS2812B4.4 (DIN)
unnamed: TP11.1, WS2812B4.2 (DOU), WS2812B5.4 (DIN)
unnamed: TP13.1, WS2812B5.2 (DOU), WS2812B6.4 (DIN)
